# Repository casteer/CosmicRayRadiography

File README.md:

# CosmicRayRadiography

The development of a cosmic ray tracking system to radiograph large structures.

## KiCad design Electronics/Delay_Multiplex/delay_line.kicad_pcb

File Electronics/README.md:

# README

## Electronics Overview

For each detector, we need to count the number of pulses on it that are coincident with others through another one place some distance away. This provides coarse measurement of the cosmic ray track.

There are two approaches to the development of the electronics (that I can think of):

1 Preamp-Discriminator for each channel and then Coincidence-Counter
2 Take all of the detector pulses into a fast digitizer and in the acquisition software, package the event information (time, pulse height, detector numbers hit) into a single event.  

Aside from a number of technical pros and cons the most basic one is: 

Option 1 is cheaper but takes alot of work
Option 2 is expensive but quick

## Requirements

The design must have or do... 

* Approximately 12 channels 
* Sub-20ns timing resolution 
* Low-power where practicable
* Minimize the number of cables to the system
* Setup must be robust over 6 to 12 months
* Enable an understanding (and mitigation) of the environmental dependence of its performance

For the intended detectors, the electronics must provide up to 1kV over the 12 channels.

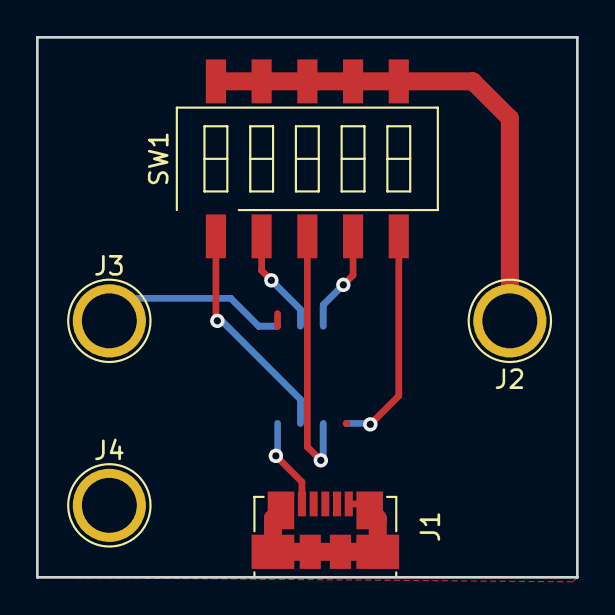
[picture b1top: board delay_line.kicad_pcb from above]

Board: 2 copper layers, 30.0 x 30.0 mm, 6 parts (1 on the bottom side), 9 nets.

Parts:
J1: USB_OTG; USB_Micro-B_Molex_47346-0001
J2, J3, J4: CONN_01X01; 1pin
SW1: SW_DIP_x05; SW_DIP_x5_W8.61mm_Slide_LowProfile
U1: DS1100-500; SOIC-8_3.9x4.9mm_Pitch1.27mm

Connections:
GNDREF: J1.5, J1.6, J4.1, U1.4
unnamed: J1.1, U1.8
unnamed: J2.1, SW1.6, SW1.7, SW1.8, SW1.9, SW1.10
unnamed: J3.1, U1.1
unnamed: SW1.1, U1.7
unnamed: SW1.2, U1.2
unnamed: SW1.3, U1.6
unnamed: SW1.4, U1.3
unnamed: SW1.5, U1.5

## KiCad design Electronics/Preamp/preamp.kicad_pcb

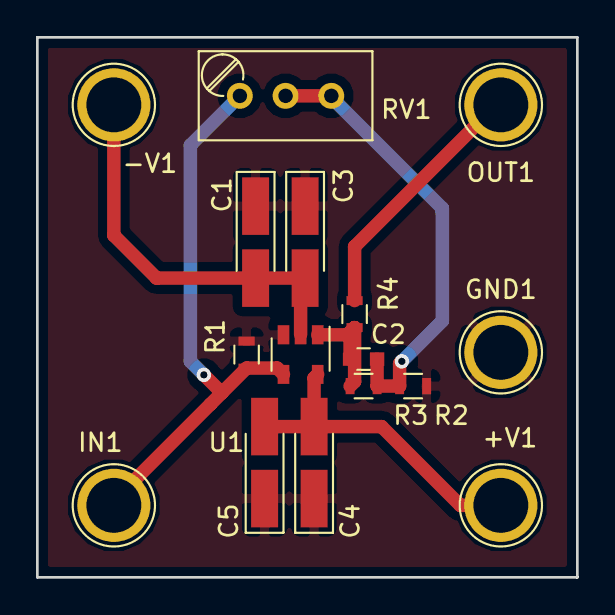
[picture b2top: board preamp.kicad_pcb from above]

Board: 2 copper layers, 30.0 x 30.0 mm, 16 parts (0 on the bottom side), 7 nets.

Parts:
+V1: +V; 1pin
-V1: -V; 1pin
C1, C4: 10uF; CP_Tantalum_Case-A_EIA-3216-18_Hand
C2: 0.5pF; C_0603
C3, C5: 0.1uF; CP_Tantalum_Case-A_EIA-3216-18_Hand
GND1: GND; 1pin
IN1: IN; 1pin
OUT1: OUT; 1pin
R1, R2, R3, R4: 50; R_0603
RV1: 500 Ohm POT_TRIM; Potentiometer_Trimmer_Bourns_3296W
U1: OPA659; SOT-23-5

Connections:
GNDREF: C1.1, C3.1, C4.1, C5.1, GND1.1, R1.1, R2.2, U1.3
unnamed: +V1.1, C4.2, C5.2, U1.5
unnamed: -V1.1, C1.2, C3.2, U1.2
unnamed: C2.1, R3.1, R4.2, U1.1
unnamed: C2.2, R2.1, R3.2, RV1.2, RV1.3
unnamed: IN1.1, R1.2, RV1.1, U1.4
unnamed: OUT1.1, R4.1

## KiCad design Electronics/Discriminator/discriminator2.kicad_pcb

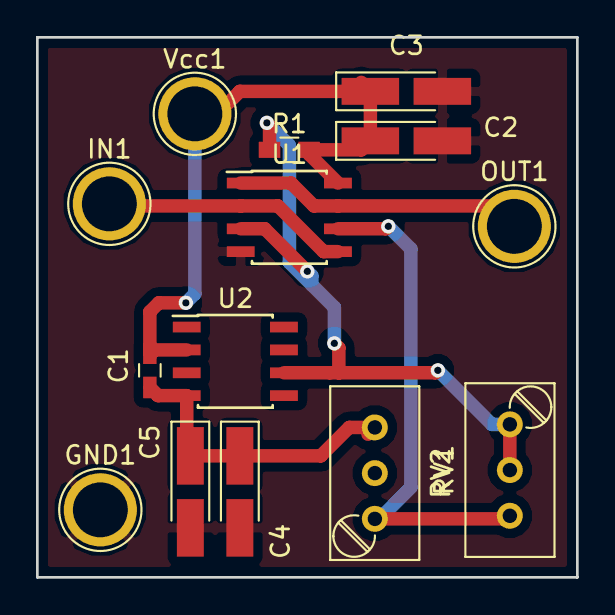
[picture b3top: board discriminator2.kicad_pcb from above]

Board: 2 copper layers, 30.0 x 30.0 mm, 14 parts (0 on the bottom side), 7 nets.

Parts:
C1: 0.1u; C_0603_HandSoldering
C2, C4: 0.1u; CP_Tantalum_Case-A_EIA-3216-18_Hand
C3, C5: 10u; CP_Tantalum_Case-A_EIA-3216-18_Hand
GND1: GND; 1pin
IN1: IN; 1pin
OUT1: OUT; 1pin
R1: 100k; R_0603_HandSoldering
RV1, RV2: 100k POT_TRIM; Potentiometer_Trimmer_Bourns_3296W
U1: LTC6702; SOIC-8_3.9x4.9mm_Pitch1.27mm
U2: MAX6029-2.5V; SOIC-8_3.9x4.9mm_Pitch1.27mm
Vcc1: Vcc; 1pin

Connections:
GNDREF: C2.2, C3.2, C4.2, C5.2, GND1.1, U1.4
unnamed: C1.2, C4.1, C5.1, RV2.3, U2.4
unnamed: IN1.1, U1.2, U1.5
unnamed: OUT1.1, U1.1, U1.7
unnamed: R1.1, RV1.1, RV1.2, U1.3, U2.6
unnamed: RV1.3, RV2.1, U1.6
VPP: C1.1, C2.1, C3.1, R1.2, U1.8, U2.2, Vcc1.1

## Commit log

2017-05-25 Rename MechanicalDesign/Readme.md to Mechanics/Readme.md
2017-05-27 Add files via upload
    Adding PMT HV base files
2017-06-09 Add files via upload
    Readout program with correct trigger in software
2017-06-09 Create Readme.md
    Added instructions for the readout software.
2017-12-08 Updated code
